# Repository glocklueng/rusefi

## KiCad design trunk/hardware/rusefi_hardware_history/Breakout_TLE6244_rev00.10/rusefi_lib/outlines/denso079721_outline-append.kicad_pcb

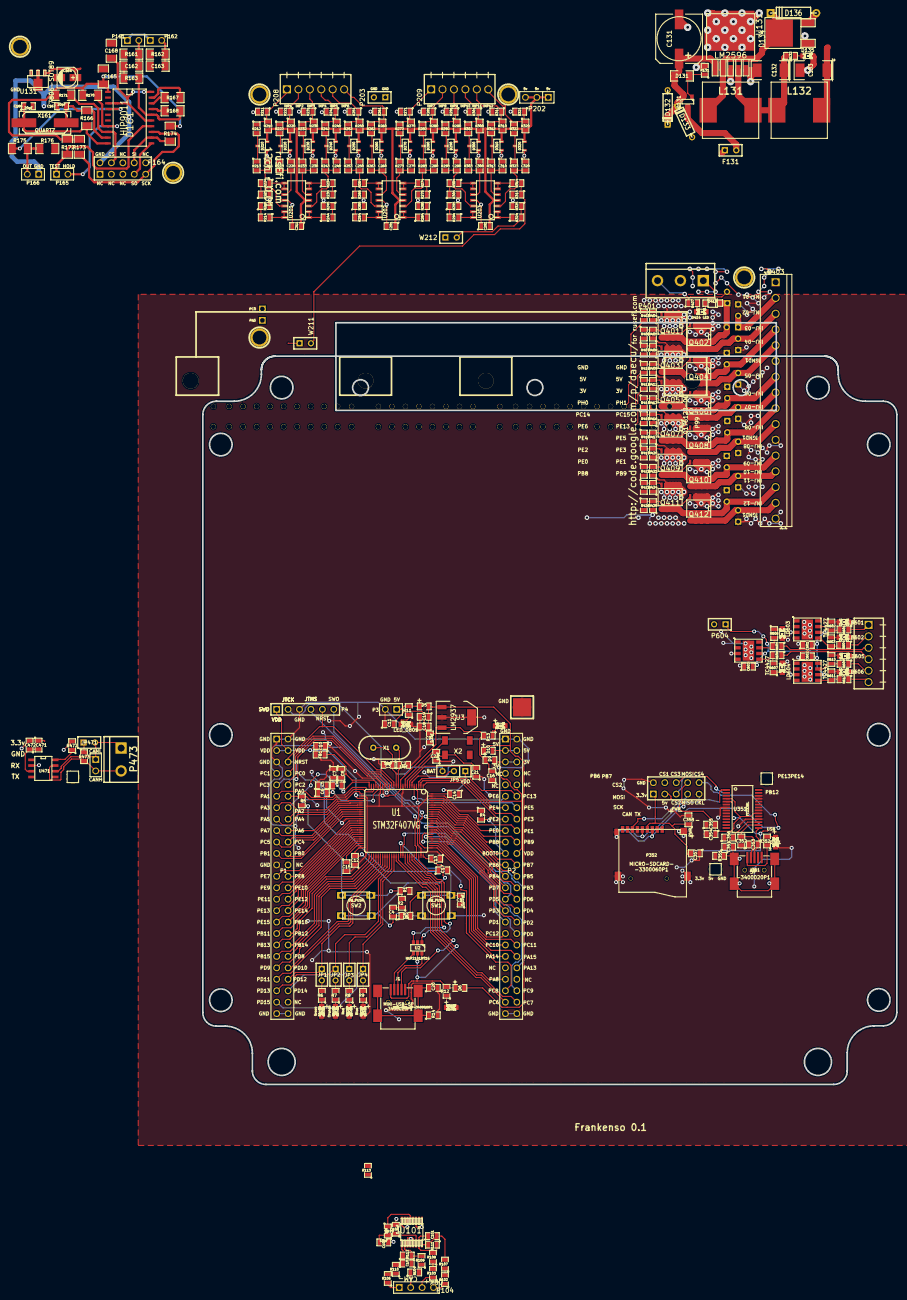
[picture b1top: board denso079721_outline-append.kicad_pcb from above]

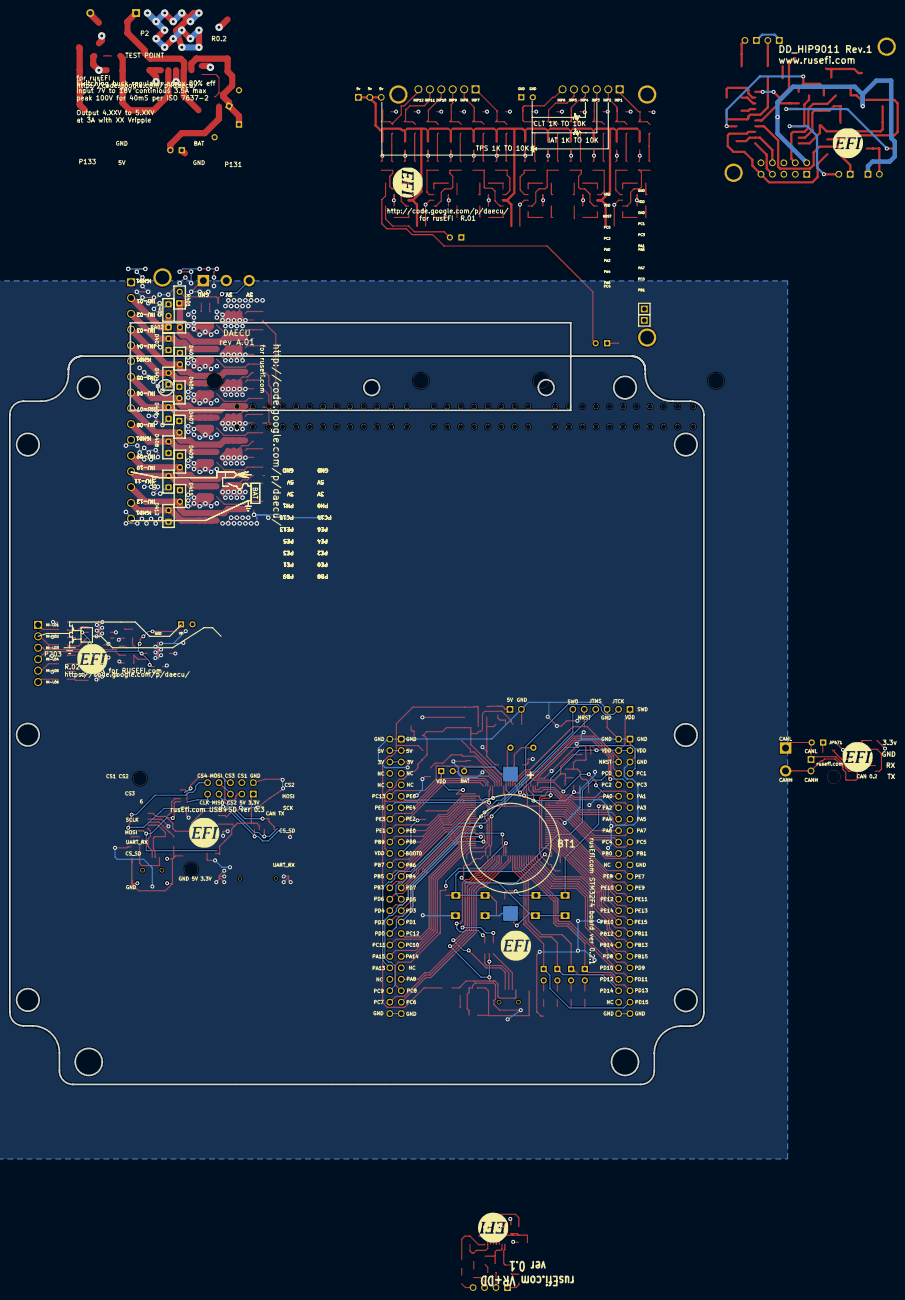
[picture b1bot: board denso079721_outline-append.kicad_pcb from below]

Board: 2 copper layers, 358 parts (24 on the bottom side), 255 nets.

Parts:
BT1: BATTERY_CR2032; BATT_CR2032_MPD
C1: 0.02uF; SM0805
C2, C3, C21, C22: 18pF; SM0805
C4, C15, C17: 2u2F; SM0805
C5, C8, C210, C220, C230, C240, C250, C260, C270, C280, C290, C300, C310, C320: 0.01uF; SM0805
C6, C7, C16: 1uF; SM0805
C9, C10, C11, C12, C13, C14, C18, C20, C104, C211, C251, C291, C601, C602, C603: 0.1uF; SM0805
C19, C354, C358, C472: 4.7uF; SM0805
C101, C102: 1000pF; SM0805
C103: 10uF; SM0805
C131: 470uF 25V; SMDSVP10
C132, C133: 220uF 16V; SM2512
C162, C163: 47n; SM1206
C164: 10u; c_elec_4x5.3
C165: 100n; SM1206
C166, C167: 20pF; SM0805
C168: 22n; SM1206
C351: 4700pF; SM0805
C352, C353: 47pF; SM0805
C355, C356, C357, C471: .1uF; SM0805
D1, D2, D3, D4, D7, D8, D11: LED_0805; LED-0805_A
D5, D6, D9, D10: DIODESCH; SM0805-diode
D131: ZENERSMALL; SM1206
D132, D133: TVS; D133
D134: SCHDPAK; DPAK2
D135: GREEN; LED-0805
D136: DIODESCH; D134
D161: HIP9011; SO20L
D210, D220, D230, D240, D250, D260, D270, D280, D290, D300, D310, D320: DOUBLE_SCHOTTKY; sot23
D351: GREEN; LED-0805_A
D401, D402, D403, D404, D405, D406, D407, D408, D409, D410, D411, D412: DIODE; SIL-2
D413: DIODE; SOD-123
D414: LED; LED-0805
F131: 3.5A; SIL-2
FB1: FILTER; SM0805
G1, G101, G161, G201, G305, G471, G601: LOGO; LOGO_F
J1, J351: MINI-USB-5P-3400020P1
JP1, JP2, JP3, JP4, JP471: JUMPER; JUMPER-2
JP5: JUMPER3; SIL-3
L131, L132: 38uH; SM100uH
LD601, LD602, LD603, LD604, LD605, LD606: LED; LED-0805
M200, M201, M202, M401: CONN_1; 1pin
M351, M352, M471: CONN_1; PIN_ARRAY_1
P1, P2: CONN_25X2; PIN_ARRAY_25x2_A
P3, P472: CONN_2; PIN_ARRAY_2_A
P4: CONN_6; PIN_ARRAY-6X1
P5: CONN_1; 1PIN_SMD
P99: 0176122-06; 176122-6
P104: CONN_4; PIN_ARRAY_4x1
P161: KNOCK 1; PIN_ARRAY_2X1
P162: KNOCK 2; PIN_ARRAY_2X1
P164: CONN_5X2; PIN_ARRAY_5x2
P165, P166: CONN_2; PIN_ARRAY_2X1
P202: CONN_3; PIN_ARRAY_3X1
P203, P604: CONN_2; SIL-2
P204, P205: CONN_1; PIN_ARRAY_1
P208, P209: CONN_6; 6_screw_term_.1in
P351: CONN_5X2; PIN_ARRAY_5x2_M
P352: MICRO-SDCARD-CONNECTOR-3300060P1
P401: CONN_3; bornier3
P403: CONN_16; SIL-16_3.5MM
P473: CONN_2; bornier2
P603: CONN_6; OSTVN06A150
Q131: MOS_PRO; SOT23
Q401, Q402, Q403, Q404, Q405, Q406, Q407, Q408, Q409, Q410, Q411, Q412: OVP_DRIVER; SO8E_ST
R1, R3, R4, R113, R114, R212, R222, R232, R242, R252, R262, R272, R282, R292, R302, R312, R322, R472: 10k; SM0805
R2: 100R; SM0805
R5: 330R; SM0805
R6, R7, R8, R9: 680R; SM0805
R10: 47R; SM0805
R11, R12, R13, R131, R132, R352: 1k; SM0805
R14: 100k; SM0805
R102, R103, R104, R106, R107, R108, R109, R110, R111, R112: 5k; SM0805
R161, R162, R166: 1M; SM1206
R163, R175, R176: 10k; SM1206
R167, R168: 68k; SM1206
R170, R171, R172, R173, R174: 1K; SM1206
R210, R220, R230, R240, R250, R260, R270, R280, R290, R300, R310, R320, R602, R603, R606, R607, R610, R611: 2700; SM0805
R211, R221, R231, R241, R251, R261, R271, R281, R291, R301, R311, R321: 500K; SM0805
R213, R223, R233, R243, R253, R263, R273, R283, R293, R303, R313, R323, R601, R604, R605, R608, R609, R612: 100; SM0805
R214, R215, R224, R225, R234, R235, R244, R245, R254, R255, R264, R265, R274, R275, R284, R285, R294, R295, R304, R305, R314, R315, R324, R325: 1500; SM0805
R351: 1M; SM0805
R401: OPT; SIL-2
R402: 0R; SIL-2
R403, R406, R407, R410, R411, R414, R415, R418, R419, R422, R423, R426: 20R; SM0805
R404, R405, R408, R409, R412, R413, R416, R417, R420, R421, R424, R425, R427: 1K; SM0805
R473: 120; SM0805
SW1, SW2: SW_PUSH; TL-1105
U1: STM32F407VG; TQFP_100
U2: NUF2101MT1G; SOT-457
U3: LM2937; SOT223
U101: MAX9926/9927; maxim-10-QSOP16
U131: LM2596; DPAK5
U131#2: 7805-SOT89; sot89
U201, U202, U203: LMV324IDR; so-14
U351: FT232RL; ssop-28
U471: SN65HVD230; SO8E
U601, U602, U603: TC4427; SOIC8-DFN
W211, W212: TEST; SIL-2
X1: CRYSTAL; HC-49V
X2: CRYSTAL(MC306); MC-306
X161: QUARTZ; Q_49U3HMS

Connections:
/3.3V: C357.2, C358.1, C471.2, C472.1, D9.2, P2.5, P2.6, P351.1, P352.4, P401.2, U471.3
/5V: C103.2, C104.1, C133.1, C211.1, C251.1, C291.2, C354.1, C355.2, D10.2, D210.3, D220.3, D230.3, D240.3, D250.3, D260.3, D270.3, D280.3, D290.3, D300.3, D310.3, D320.3, L132.2, P2.3, P2.4, P202.1, P202.2, P202.3, P351.3, P401.3, R113.1, R114.2, R210.2, R220.2, R230.2, R240.2, R250.2, R260.2, R270.2, R280.2, R290.2, R300.2, R310.2, R320.2, R401.2, R427.1, U101.14, U201.4, U202.4, U203.4, U351.4, U351.20
/5Vi: C18.2, C19.1, D5.2, D6.2, D10.1, U3.1
/+5V: C165.1, D161.1, R170.1, R171.1, R172.1, R173.1, R174.1
/BOOT0: P2.21, R4.2, U1.94
/CAM: R114.1, U101.5
/CAM+: P104.1, R106.1
/CAM-: P104.2, R104.1
/CANH: P472.2, P473.2, R473.2, U471.7
/CANL: JP471.2, P472.1, P473.1, U471.6
/CRANK: R113.2, U101.4
/CRK2+: P104.4, R102.1
/CRK2-: P104.3, R103.1
/CS: D161.8, P164.4, R171.2
/D+: C353.2, J1.3, J351.3, U2.6, U351.15
/D-: C352.2, J1.2, J351.2, U2.4, U351.16
/FB: C132.1, L131.2, L132.1, R132.1, U131.4
/GND: C164.2, C165.2, C166.2, C167.2, C168.2, D161.2, P161.1, P162.1, P164.2, P166.1, R161.2, R162.2, R176.2, U131#2.2
/HL1: P603.1, R601.1
/HL2: P603.2, R604.1
/HL3: P603.3, R605.1
/HL4: P603.4, R608.1
/HL5: P603.5, R609.1
/HL6: P603.6, R612.1
/INJ-01: D413.2, Q401.2, R401.1, R402.2
/INJ-01_2: D401.2, P403.2, R402.1
/INJ-02: D402.2, P403.3, Q402.2
/INJ-03: D403.2, P403.4, Q403.2
/INJ-04: D404.2, P403.5, Q404.2
/INJ-05: D405.2, P403.7, Q405.2
/INJ-06: D406.2, P403.8, Q406.2
/INJ-07: D407.2, P403.9, Q407.2
/INJ-08: D408.2, P403.10, Q408.2
/INJ-09: D409.2, P403.12, Q409.2
/INJ-10: D410.2, P403.13, Q410.2
/INJ-11: D411.2, P403.14, Q411.2
/INJ-12: D412.2, P403.15, Q412.2
/INP1: P208.1, R210.1, R211.1, R212.1
/INP2: P208.2, R220.1, R221.1, R222.1
/INP3: P208.3, R230.1, R231.1, R232.1
/INP4: P208.4, R240.1, R241.1, R242.1
/INP5: P208.5, R250.1, R251.1, R252.1
/INP6: P208.6, R260.1, R261.1, R262.1
/INP7: P209.1, R270.1, R271.1, R272.1
/INP8: P209.2, R280.1, R281.1, R282.1
/INP9: P209.3, R290.1, R291.1, R292.1
/INP10: P209.4, R300.1, R301.1, R302.1
/INP11: P209.5, R310.1, R311.1, R312.1
/INP12: P209.6, R320.1, R321.1, R322.1
/INT/HLD: D161.7, P165.2, R170.2
/INTOUT: D161.4, R175.1
/NRST: C1.2, P1.6, P4.5, R3.2, SW1.1, U1.14
/OUT: D134.2, D136.2, L131.1, P166.2, R175.2, R176.1, U131.2
/PA0: P1.12, R5.1, R254.2, R255.1, U1.23
/PA1: P1.11, R214.2, R215.1, U1.24
/PA2: P1.14, R284.2, R285.1, U1.25
/PA3: P1.13, R224.2, R225.1, U1.26
/PA4: P1.16, R274.2, R275.1, U1.29
/PA5: P1.15, P204.1, U1.30
/PA6: P1.18, R294.2, R295.1, U1.31
/PA7: P1.17, R304.2, R305.1, U1.32
/PA8: P2.43, U1.67
/PA9: D6.1, J1.1, R12.2, U1.68, U2.5
/PA10: J1.4, U1.69
/PA11: U1.70, U2.3
/PA12: U1.71, U2.1
/PA13: P2.42, P4.4, U1.72
/PA14: P2.39, P4.2, U1.76
/PA15: P2.40, U1.77
/PB0: P1.22, U1.35
/PB1: P1.21, U1.36
/PB3: P2.28, P4.6, P351.9, P352.5, U1.89
/PB4: P2.25, P351.7, P352.7, U1.90
/PB5: P2.26, P351.8, P352.3, U1.91
/PB6: P2.23, U1.92, U471.1
/PB7: P2.24, U1.93
/PB8: P2.19, R423.2, U1.95
/PB9: P2.20, R426.2, U1.96
/PB10: P1.34, U1.47
/PB11: P1.35, U1.48
/PB12: P1.36, U1.51, U471.4
/PB13: P1.37, U1.52
/PB14: P1.38, U1.53
/PB15: P1.39, U1.54
/PC0: P1.8, P205.1, U1.15
/PC1: P1.7, R244.2, R245.1, U1.16
/PC2: P1.10, R264.2, R265.1, U1.17
/PC3: P1.9, R234.2, R235.1, U1.18
/PC4: P1.20, U1.33, W211.1
/PC5: P1.19, U1.34, W212.1
/PC6: P2.47, U1.63
/PC7: P2.48, U1.64, U603.2
/PC8: P2.45, U1.65
/PC9: P2.46, U1.66, U603.4
/PC10: P2.37, U1.78, U351.5
/PC11: P2.38, U1.79, U351.1
/PC12: P2.35, U1.80
/PC13: P2.12, R410.2, U1.7
/PD0: P2.36, U1.81
/PD1: P2.33, U1.82
/PD2: P2.34, U1.83
/PD3: P2.31, U1.84
/PD4: P2.32, P352.2, U1.85
/PD5: P2.29, U1.86
/PD6: P2.30, U1.87
/PD7: P2.27, U1.88
/PD8: P1.40, U1.55
/PD9: P1.41, U1.56
/PD10: P1.42, U1.57
/PD11: P1.43, U1.58
/PD12: JP1.1, P1.44, U1.59
/PD13: JP2.1, P1.45, U1.60
/PD14: JP3.1, P1.46, U1.61
/PD15: JP4.1, P1.47, U1.62
/PE0: P2.17, R419.2, U1.97
/PE1: P2.18, R422.2, U1.98
/PE2: P2.15, R415.2, U1.1
/PE3: P2.16, R418.2, U1.2
/PE4: P2.13, R411.2, U1.3
/PE5: P2.14, R414.2, U1.4
/PE6: P2.11, R407.2, U1.5
/PE7: P1.25, U1.38
/PE8: P1.26, U1.39, U601.4
/PE9: P1.27, U1.40
/PE10: P1.28, U1.41, U602.2
/PE11: P1.29, U1.42
/PE12: P1.30, U1.43, U601.2
/PE13: P1.31, U1.44
/PE14: P1.32, U1.45, U602.4
/PE15: P1.33, U1.46
/SCK: D161.13, P164.9, R173.2
/SI: D161.12, P164.8, R174.2
/SO: D161.11, P164.7
/TEST: D161.14, P165.1, R172.2
/VBAT: C131.1, D131.2, D132.2, D133.2, Q131.2, U131.1
/VDD: C4.1, C9.2, C10.2, C11.2, C12.2, C13.2, C14.2, C16.2, D9.1, FB1.2, JP5.1, P1.3, P1.4, P2.22, P4.1, R3.1, R13.2, SW2.2, U1.11, U1.19, U1.28, U1.50, U1.75, U1.100, U3.3
/VP: C601.2, C602.2, C603.2, P604.1, U601.6, U602.6, U603.6
/Vf: F131.2, Q131.3
F-000087: C3.1, U1.13, X1.1
F-000088: C17.1, U1.73
F-000089: C2.1, U1.12, X1.2
F-000090: C15.1, U1.49
F-000091: C7.2, C8.2, FB1.1, R10.1, U1.22
F-000092: JP5.2, U1.6
F-000093: BT1.1, JP5.3
F-000094: C4.2, R2.1
F-000095: R1.1, R2.2, R5.2, SW2.1
F-000096: JP3.2, R8.2
F-000097: JP4.2, R9.2
F-000098: JP1.2, R6.2
F-000099: JP2.2, R7.2
F-0000100: D7.1, R11.1
F-0000101: D5.1, P3.1, R11.2
F-0000102: D8.1, R12.1
F-0000103: D2.1, R7.1
F-0000104: D3.1, R8.1
F-0000105: D4.1, R9.1
F-0000106: D11.1, R13.1
F-0000107: C20.1, J1.6, R14.1
F-0000108: C5.2, C6.2, R10.2, U1.21
F-0000109: D1.1, R6.1
F-0000110: C21.2, U1.8, X2.1
F-0000111: C22.2, U1.9, X2.4
F-0000129: R102.2, R107.1
F-0000130: R104.2, R109.1
F-0000132: R106.2, R110.1
F-0000133: R103.2, R108.1
F-0000134: C101.1, R108.2, R111.1, U101.15
F-0000135: C101.2, R107.2, R111.2, U101.16
F-0000136: C102.1, R110.2, R112.1, U101.9
F-0000137: C102.2, R109.2, R112.2, U101.10
F-0000144: D131.1, Q131.1, R131.1
F-0000145: D135.1, R132.2
F-0000155: C167.1, D161.9, R166.2, X161.2
F-0000156: C163.1, P162.2, R162.1
F-0000158: C166.1, D161.10, R166.1, X161.1
F-0000159: C168.1, D161.3, D161.15, D161.20
F-0000160: D161.16, R163.2, R168.2
F-0000161: D161.17, R168.1
F-0000162: D161.18, R167.1
F-0000163: D161.19, R167.2
F-0000164: C162.2, R163.1
F-0000165: C162.1, P161.2, R161.1
F-0000167: C164.1, U131#2.1
F-0000192: D280.2, R282.2, R283.1
F-0000193: R214.1, U201.13, U201.14
F-0000194: R224.1, U201.8, U201.9
F-0000195: D270.2, R272.2, R273.1
F-0000196: R244.1, U201.1, U201.2
F-0000197: D300.2, R302.2, R303.1
F-0000198: D290.2, R292.2, R293.1
F-0000199: R304.1, U203.8, U203.9
F-0000200: R294.1, U203.13, U203.14
F-0000201: C290.2, R293.2, U203.12
F-0000202: D250.2, R252.2, R253.1
F-0000203: C300.2, R303.2, U203.10
F-0000204: R314.1, U203.6, U203.7
F-0000205: R324.1, U203.1, U203.2
F-0000206: C310.2, R313.2, U203.5
F-0000207: C320.2, R323.2, U203.3
F-0000208: D320.2, R322.2, R323.1
F-0000209: D260.2, R262.2, R263.1
F-0000210: D310.2, R312.2, R313.1
F-0000211: R324.2, R325.1, W212.2
F-0000212: R314.2, R315.1, W211.2
F-0000213: C250.2, R253.2, U202.12
F-0000214: D210.2, R212.2, R213.1
F-0000215: R254.1, U202.13, U202.14
F-0000216: R274.1, U202.6, U202.7
F-0000217: R264.1, U202.8, U202.9
F-0000218: C240.2, R243.2, U201.3
F-0000219: C230.2, R233.2, U201.5
F-0000220: C270.2, R273.2, U202.5
F-0000221: C280.2, R283.2, U202.3
F-0000222: C220.2, R223.2, U201.10
F-0000223: D220.2, R222.2, R223.1
F-0000224: C210.2, R213.2, U201.12
F-0000225: C260.2, R263.2, U202.10
F-0000226: R284.1, U202.1, U202.2
F-0000227: D240.2, R242.2, R243.1
F-0000229: D230.2, R232.2, R233.1
F-0000230: R234.1, U201.6, U201.7
F-0000249: J351.1, R352.1
F-0000250: C351.2, J351.6, R351.1
F-0000251: D351.1, R352.2
F-0000270: C356.2, U351.17
F-0000312: Q408.1, R417.2, R418.1
F-0000313: Q404.1, R409.2, R410.1
F-0000314: Q406.1, R413.2, R414.1
F-0000315: Q402.1, R405.2, R406.1
F-0000316: D414.1, R427.2
F-0000317: Q410.1, R421.2, R422.1
F-0000318: D413.1, D414.2
F-0000319: Q412.1, R425.2, R426.1
F-0000320: Q401.1, R403.1, R404.2
F-0000321: Q405.1, R411.1, R412.2
F-0000322: Q403.1, R407.1, R408.2
F-0000323: Q409.1, R419.1, R420.2
F-0000324: Q407.1, R415.1, R416.2
F-0000325: Q411.1, R423.1, R424.2
F-0000332: JP471.1, R473.1
F-0000333: R472.1, U471.8
F-0000347: LD604.1, R607.1
F-0000348: LD601.1, R602.1
F-0000349: R609.2, R610.2, U603.7
F-0000350: LD602.1, R603.1
F-0000351: R603.2, R604.2, U601.5
F-0000352: R601.2, R602.2, U601.7
F-0000353: R607.2, R608.2, U602.5
F-0000354: R605.2, R606.2, U602.7
F-0000355: LD606.1, R611.1
F-0000356: R611.2, R612.2, U603.5
F-0000357: LD605.1, R610.1
F-0000358: LD603.1, R606.1
GND: BT1.2, C1.1, C2.2, C3.2, C5.1, C6.1, C7.1, C8.1, C9.1, C10.1, C11.1, C12.1, C13.1, C14.1, C15.2, C16.1, C17.2, C18.1, C19.2, C20.2, C21.1, C22.1, C103.1, C104.2, C131.2, C132.2, C133.2, C210.1, C211.2, C220.1, C230.1, C240.1, C250.1, C251.2, C260.1, C270.1, C280.1, C290.1, C291.1, C300.1, C310.1, C320.1, C351.1, C352.1, C353.1, C354.2, C355.1, C356.1, C357.1, C358.2, C471.1, C472.2, C601.1, C602.1, C603.1, D1.2, D2.2, D3.2, D4.2, D7.2, D8.2, D11.2, D132.1, D133.1, D134.1, D134.3, D135.2, D136.1, D210.1, D220.1, D230.1, D240.1, D250.1, D260.1, D270.1, D280.1, D290.1, D300.1, D310.1, D320.1, D351.2, D401.1, D402.1, D403.1, D404.1, D405.1, D406.1, D407.1, D408.1, D409.1, D410.1, D411.1, D412.1, J1.5, J351.5, LD601.2, LD602.2, LD603.2, LD604.2, LD605.2, LD606.2, P1.1, P1.2, P1.5, P1.23, P1.49, P1.50, P2.1, P2.2, P2.49, P2.50, P3.2, P4.3, P5.1, P203.1, P203.2, P351.2, P352.6, P352.G1, P352.G2, P352.G3, P352.G4, P401.1, P403.1, P403.6, P403.11, P403.16, Q401.3, Q402.3, Q403.3, Q404.3, Q405.3, Q406.3, Q407.3, Q408.3, Q409.3, Q410.3, Q411.3, Q412.3, R1.2, R4.1, R14.2, R131.2, R211.2, R215.2, R221.2, R225.2, R231.2, R235.2, R241.2, R245.2, R251.2, R255.2, R261.2, R265.2, R271.2, R275.2, R281.2, R285.2, R291.2, R295.2, R301.2, R305.2, R311.2, R315.2, R321.2, R325.2, R351.2, R404.1, R405.1, R408.1, R409.1, R412.1, R413.1, R416.1, R417.1, R420.1, R421.1, R424.1, R425.1, R472.2, SW1.2, U1.10, U1.20, U1.27, U1.37, U1.74, U1.99, U2.2, U3.2, U3.4, U101.1, U101.3, U101.6, U101.8, U101.11, U101.12, U101.13, U131.3, U131.5, U201.11, U202.11, U203.11, U351.7, U351.18, U351.21, U351.25, U351.26, U471.2, U601.3, U601.9, U602.3, U602.9, U603.3, U603.9

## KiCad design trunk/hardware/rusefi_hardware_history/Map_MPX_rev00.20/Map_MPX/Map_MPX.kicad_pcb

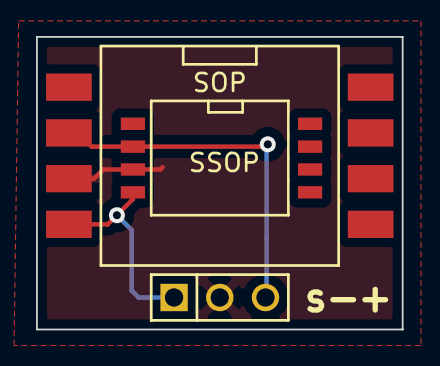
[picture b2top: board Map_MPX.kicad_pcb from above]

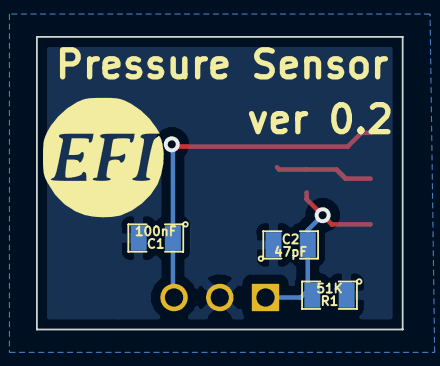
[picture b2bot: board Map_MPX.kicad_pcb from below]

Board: 2 copper layers, 20.3 x 16.3 mm, 4 parts (3 on the bottom side), 2 nets.

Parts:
C1: 100nF; SM0805
C2: 47pF; SM0805
R1: 51K; SM0805
SSOP: SOP; SSOP

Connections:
GND: C1.2, C2.1, R1.1
unnamed: C2.2, R1.2

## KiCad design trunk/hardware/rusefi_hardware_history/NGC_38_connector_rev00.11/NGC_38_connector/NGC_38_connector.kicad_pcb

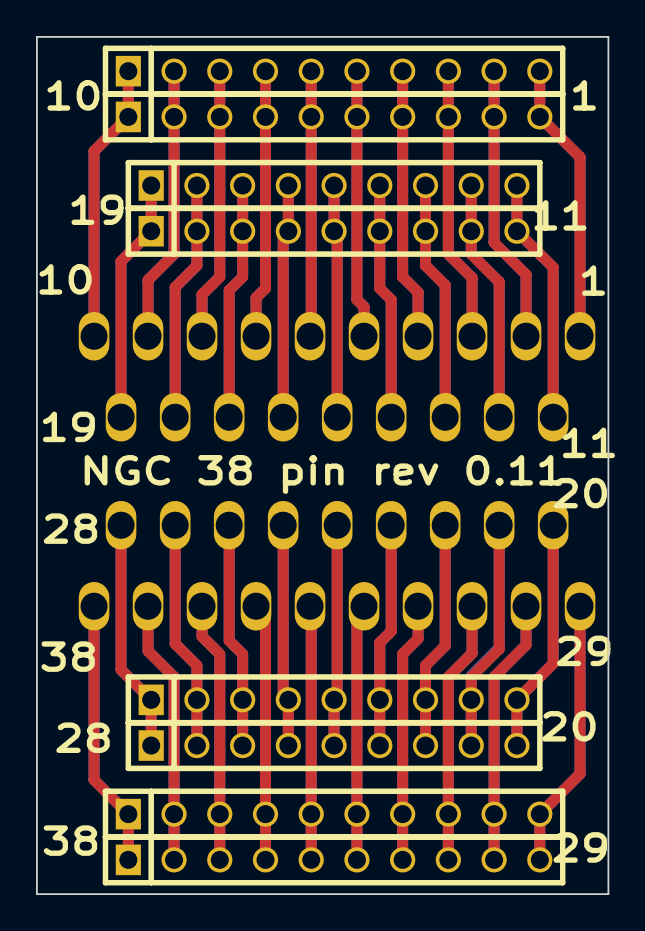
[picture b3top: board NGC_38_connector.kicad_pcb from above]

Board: 2 copper layers, 31.8 x 47.6 mm, 9 parts (0 on the bottom side), 38 nets.

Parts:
P1: DIL38; PCM_C1
P2, P4, P6, P9: CONN_10; SIL-10
P3, P5, P7, P8: CONN_9; SIL-9

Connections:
unnamed: P1.1, P2.1, P6.1
unnamed: P1.2, P2.2, P6.2
unnamed: P1.3, P2.3, P6.3
unnamed: P1.4, P2.4, P6.4
unnamed: P1.5, P2.5, P6.5
unnamed: P1.6, P2.6, P6.6
unnamed: P1.7, P2.7, P6.7
unnamed: P1.8, P2.8, P6.8
unnamed: P1.9, P2.9, P6.9
unnamed: P1.10, P2.10, P6.10
unnamed: P1.17, P3.7, P7.7
unnamed: P1.24, P5.5, P8.5
unnamed: P1.25, P5.6, P8.6
unnamed: P1.26, P5.7, P8.7
unnamed: P1.27, P5.8, P8.8
unnamed: P1.28, P5.9, P8.9
unnamed: P1.11, P3.1, P7.1
unnamed: P1.12, P3.2, P7.2
unnamed: P1.13, P3.3, P7.3
unnamed: P1.14, P3.4, P7.4
unnamed: P1.15, P3.5, P7.5
unnamed: P1.16, P3.6, P7.6
unnamed: P1.23, P5.4, P8.4
unnamed: P1.18, P3.8, P7.8
unnamed: P1.19, P3.9, P7.9
unnamed: P1.31, P4.3, P9.3
unnamed: P1.29, P4.1, P9.1
unnamed: P1.30, P4.2, P9.2
unnamed: P1.32, P4.4, P9.4
unnamed: P1.33, P4.5, P9.5
unnamed: P1.34, P4.6, P9.6
unnamed: P1.35, P4.7, P9.7
unnamed: P1.36, P4.8, P9.8
unnamed: P1.37, P4.9, P9.9
unnamed: P1.38, P4.10, P9.10
unnamed: P1.20, P5.1, P8.1
unnamed: P1.21, P5.2, P8.2
unnamed: P1.22, P5.3, P8.3

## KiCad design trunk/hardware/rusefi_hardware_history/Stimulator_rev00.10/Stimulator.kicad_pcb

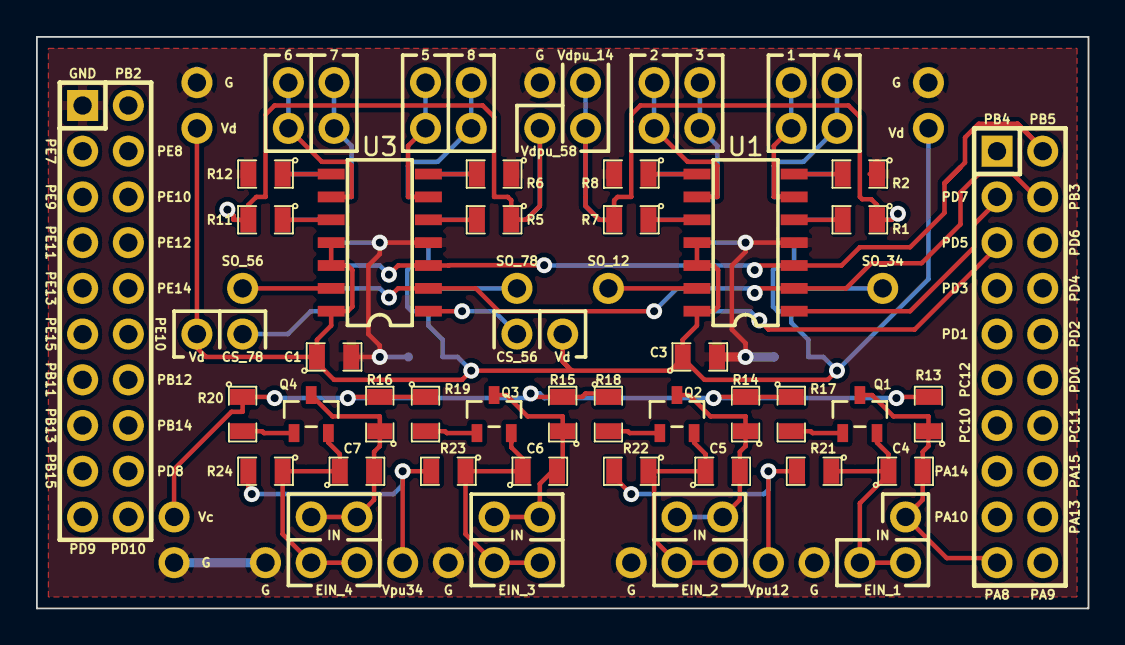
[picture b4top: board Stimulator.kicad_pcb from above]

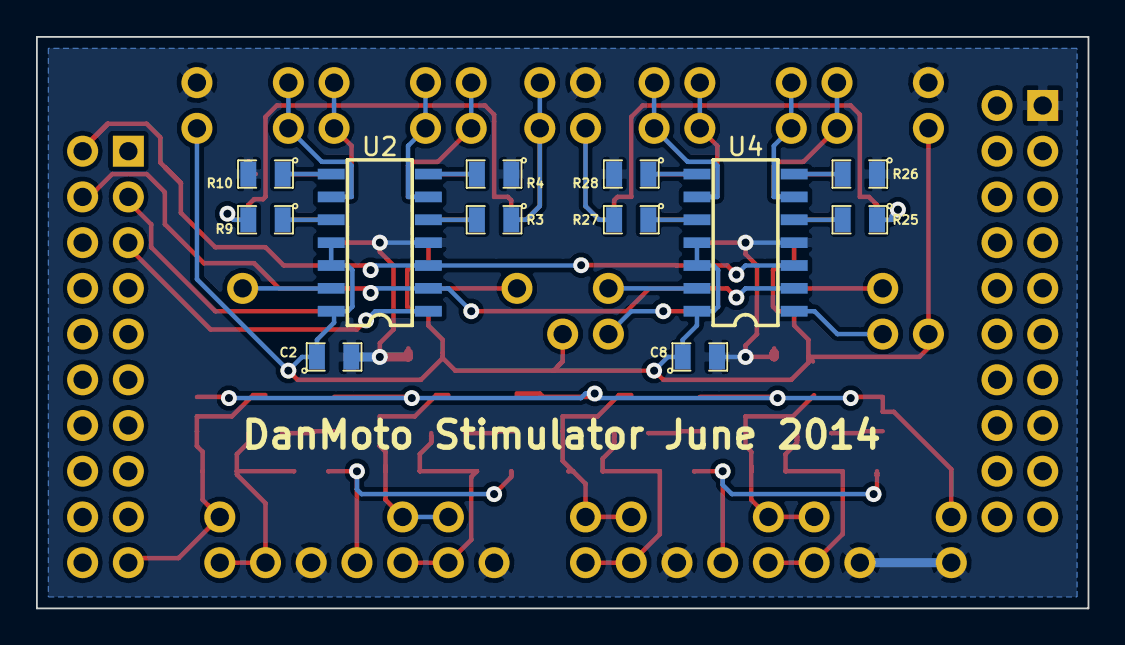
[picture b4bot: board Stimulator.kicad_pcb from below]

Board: 2 copper layers, 58.4 x 31.8 mm, 101 parts (12 on the bottom side), 53 nets.

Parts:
C1, C2, C3, C8: 0.1uF; SM0805
C4, C5, C6, C7: 100 pF; SM0805
P1, P3, P4, P5, P6, P7, P8, P9, P10, P11, P12, P13, P14, P15, P16, P17, P18, P19, P20, P21, P22, P23, P24, P25, P26, P27, P28, P29, P30, P31, P32, P33, P34, P35, P36, P38, P39, P40, P41, P42, P43, P44, P45, P46, P47, P48, P49, P50, P51, P52, P53, P54, P55, P56, P57: CONN_1; 1PIN_A
P2, P37: CONN_10X2; Pin_Header_Straight_2x10
Q1, Q2, Q3, Q4: 2N7002; sot23
R1, R2, R3, R4, R5, R6, R7, R8, R9, R10, R11, R12, R25, R26, R27, R28: 0; SM0805
R13, R14, R15, R16, R17, R18, R19, R20, R21, R22, R23, R24: 10k; SM0805
U1, U2, U3, U4: MCP42010; SOIC-14_Narrow

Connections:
/CS_12: P37.3, U1.1
/CS_34: P37.5, U2.1
/CS_56: P45.1, U3.1
/CS_78: P46.1, U4.1
/EIN_1: C4.1, P28.1, P29.1, Q1.2, R21.1
/EIN_2: C5.1, P30.1, P31.1, Q2.2, R22.1
/EIN_3: C6.1, P32.1, P33.1, Q3.2, R23.1
/EIN_4: C7.1, P34.1, P35.1, Q4.2, R24.1
/IN_1: C4.2, P20.1, P37.19, Q1.3, R13.1
/IN_2: C5.2, P21.1, P22.1, Q2.3, R14.1
/IN_3: C6.2, P23.1, P24.1, Q3.3, R15.1
/IN_4: C7.2, P25.1, P26.1, Q4.3, R16.1
/MOSI: P37.2, U1.3, U2.3, U3.3, U4.3
/OUT1: P4.1, P5.1, U1.6
/OUT2: P14.1, P15.1, U1.9
/OUT3: P6.1, P7.1, U2.6
/OUT4: P16.1, P17.1, U2.9
/OUT5: P8.1, P9.1, U3.6
/OUT6: P18.1, P19.1, U3.9
/OUT7: P47.1, P48.1, U4.6
/OUT8: P50.1, P51.1, U4.9
/SCK: P37.4, U1.2, U2.2, U3.2, U4.2
/Vc: P27.1, R13.2, R14.2, R15.2, R16.2, R17.1, R18.1, R19.1, R20.1
/Vd: C1.1, C2.1, C3.1, C8.1, P13.1, P53.1, P55.1, P56.1, U1.11, U1.12, U1.14, U2.11, U2.12, U2.14, U3.11, U3.12, U3.14, U4.11, U4.12, U4.14
/Vdpu_14: P3.1, P57.1, R1.1, R3.1, R7.2, R9.2
/Vdpu_58: P52.1, R5.1, R11.2, R25.1, R27.2
/Vipu12: P36.1, R21.2, R22.2
/Vipu34: P54.1, R23.2, R24.2
GND: C1.2, C2.2, C3.2, C8.2, P1.1, P2.1, P38.1, P39.1, P40.1, P41.1, P42.1, P43.1, P44.1, R2.1, R4.1, R6.1, R8.2, R10.2, R12.2, R26.1, R28.2, U1.4, U2.4, U3.4, U4.4
unnamed: P10.1, U1.13
unnamed: P11.1, U2.13
unnamed: P12.1, U3.13
unnamed: P49.1, U4.13
unnamed: Q1.1, R17.2
unnamed: Q2.1, R18.2
unnamed: Q3.1, R19.2
unnamed: Q4.1, R20.2
unnamed: R1.2, U1.5
unnamed: R2.2, U1.7
unnamed: R3.2, U2.5
unnamed: R4.2, U2.7
unnamed: R5.2, U3.5
unnamed: R6.2, U3.7
unnamed: R7.1, U1.10
unnamed: R8.1, U1.8
unnamed: R9.1, U2.10
unnamed: R10.1, U2.8
unnamed: R11.1, U3.10
unnamed: R12.1, U3.8
unnamed: R25.2, U4.5
unnamed: R26.2, U4.7
unnamed: R27.1, U4.10
unnamed: R28.1, U4.8

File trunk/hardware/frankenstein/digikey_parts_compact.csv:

### this file was generated by rusEfi bom_builder on Sat Feb 22 11:01:39 CST 2014
### 292 components in 2047 lines of frankenstein.cmp
### 65 kinds of components in input file
### 9 entries in BOM dictionary bom_dictionary_digikey.csv
### 2 entries in ignore list
### no BOM record for 1pin_CONN_1
### no BOM record for LED-0805_GREEN
### no BOM record for LED-0805_LED
### no BOM record for LED-0805_RED
### no BOM record for LED-1206_LED
### no BOM record for MICRO-SDCARD-CONNECTOR-3300060P1_MICRO-SDCARD-CONNECTOR-3300060P1
### no BOM record for OSTVN06A150_CONN_6
### no BOM record for PIN_ARRAY-6X1_CONN_6
### no BOM record for PIN_ARRAY_10X2_CONN_10X2
### no BOM record for PIN_ARRAY_10X2_M_CONN_10X2
### no BOM record for PIN_ARRAY_1_CONN_1
### no BOM record for PIN_ARRAY_2X1_CONN_2
### no BOM record for PIN_ARRAY_2_A_CONN_2
### no BOM record for PIN_ARRAY_2_A_JUMPER
### no BOM record for PIN_ARRAY_3X1_CONN_3
### no BOM record for PIN_ARRAY_3_A_CONN_3
### no BOM record for PIN_ARRAY_4x1_CONN_4
### no BOM record for PIN_ARRAY_5x2_CONN_5X2
### no BOM record for SIL-16_3.5MM_CONN_16
### no BOM record for SIL-2_0R
### no BOM record for SIL-2_CONN_2
### no BOM record for SIL-2_DIODE
### no BOM record for SIL-2_JUMPER
### no BOM record for SIL-2_OPT
### no BOM record for SIL-2_TEST
### no BOM record for SM0805_.1uF
### no BOM record for SM0805_0.01uF
### no BOM record for SM0805_0.1uF
### no BOM record for SM0805_100
### no BOM record for SM0805_1000pF
### no BOM record for SM0805_10K
### no BOM record for SM0805_10k
### no BOM record for SM0805_10uF
### no BOM record for SM0805_120
### no BOM record for SM0805_1500
### no BOM record for SM0805_1K
### no BOM record for SM0805_1M
### no BOM record for SM0805_1uF
### no BOM record for SM0805_20K
### no BOM record for SM0805_2700
### no BOM record for SM0805_4.7uF
### no BOM record for SM0805_4700pF
### no BOM record for SM0805_47pF
### no BOM record for SM0805_500K
### no BOM record for SM0805_5k
### no BOM record for SM0805_LED
### no BOM record for SM1206_LED
### no BOM record for SOD-123_DIODE
### no BOM record for bornier3_CONN_3
### no BOM record for pin_array_10x2_CONN_10X2
### no BOM record for pin_array_3x2_CONN_3X2
### no BOM record for pin_array_4x2_CONN_4X2
### no BOM record for sot23_DOUBLE_SCHOTTKY
### no BOM record for uMAX-uSOP_10_MAX9939




1,670-1190-1-ND,mini USB socket
4,P1.0KACT-ND,some reference
12,P20.0CCT-ND,driver current limiting
1,296-11654-1-ND,CAN driver
12,497-11082-1-ND,12A low-side MOSFET
1,MAX9926UAEE+TCT-ND,VR chip
3,TC4427AVOA-ND,1.5A dual driver
3,497-4943-1-ND,quad op-amp
1,768-1007-1-ND,USB TTL chip

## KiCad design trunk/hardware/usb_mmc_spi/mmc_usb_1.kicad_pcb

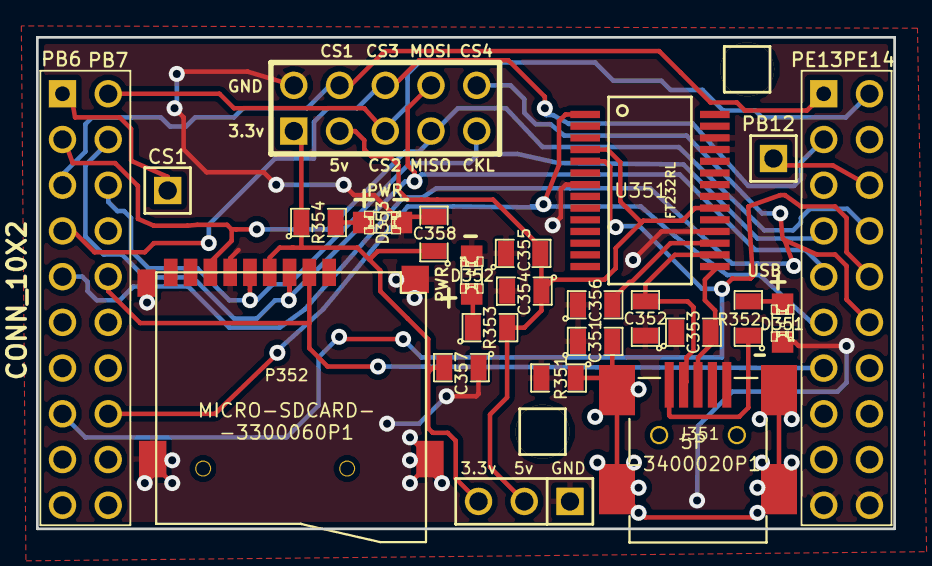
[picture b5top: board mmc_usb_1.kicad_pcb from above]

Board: 2 copper layers, 47.6 x 27.3 mm, 27 parts (1 on the bottom side), 23 nets.

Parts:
C351: 4700pF; SM0805
C352, C353: 47pF; SM0805
C354, C358: 4.7uF; SM0805
C355, C356, C357: .1uF; SM0805
D351: GREEN; LED-0805_A
D352, D353: RED; LED-0805_A
G305: LOGO; LOGO_F
J351: MINI-USB-5P-3400020P1
K351: CONN_3; PIN_ARRAY_3_A
M351, M352: CONN_1; PIN_ARRAY_1
P351: CONN_5X2; PIN_ARRAY_5x2_M
P352: MICRO-SDCARD-CONNECTOR-3300060P1
P353, P354: CONN_10X2; PIN_ARRAY_10X2_M
P355, P356: CONN_1; PIN_ARRAY_1
R351: 1M; SM0805
R352, R353, R354: 1k; SM0805
U351: FT232RL; ssop-28

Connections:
/3.3V: C357.2, C358.1, K351.3, P351.1, P352.4, R354.1
/5V: C354.1, C355.2, K351.2, P351.3, R353.2, U351.4, U351.20
/CAN_TX: P353.1, P356.1
/CS1: P351.4, P353.5, P354.1
/CS2: P351.5, P353.2, P354.2
/CS3: P351.6, P353.7, P354.3
/CS4: P351.10, P353.9, P354.12
/CS_SD_MODULE: P352.2, P353.10, P354.13
/D+: C353.2, J351.3, U351.15
/D-: C352.2, J351.2, U351.16
/SPI_MISO: P351.7, P352.7, P353.3, P354.8
/SPI_MOSI: P351.8, P352.3, P353.4, P354.9
/SPI_SCK: P351.9, P352.5, P353.6, P354.7
/USART_RX: P353.16, P354.11, U351.1
/USART_TX: P353.15, P354.10, U351.5
GND: C351.1, C352.1, C353.1, C354.2, C355.1, C356.1, C357.1, C358.2, D351.2, D352.2, D353.2, J351.5, K351.1, P351.2, P352.6, P352.G1, P352.G2, P352.G3, P352.G4, P354.19, P354.20, R351.2, U351.7, U351.18, U351.21, U351.25, U351.26
unnamed: J351.1, R352.1
unnamed: C351.2, J351.6, R351.1
unnamed: D351.1, R352.2
unnamed: D353.1, R354.2
unnamed: D352.1, R353.1
unnamed: P354.6, P355.1
unnamed: C356.2, U351.17
